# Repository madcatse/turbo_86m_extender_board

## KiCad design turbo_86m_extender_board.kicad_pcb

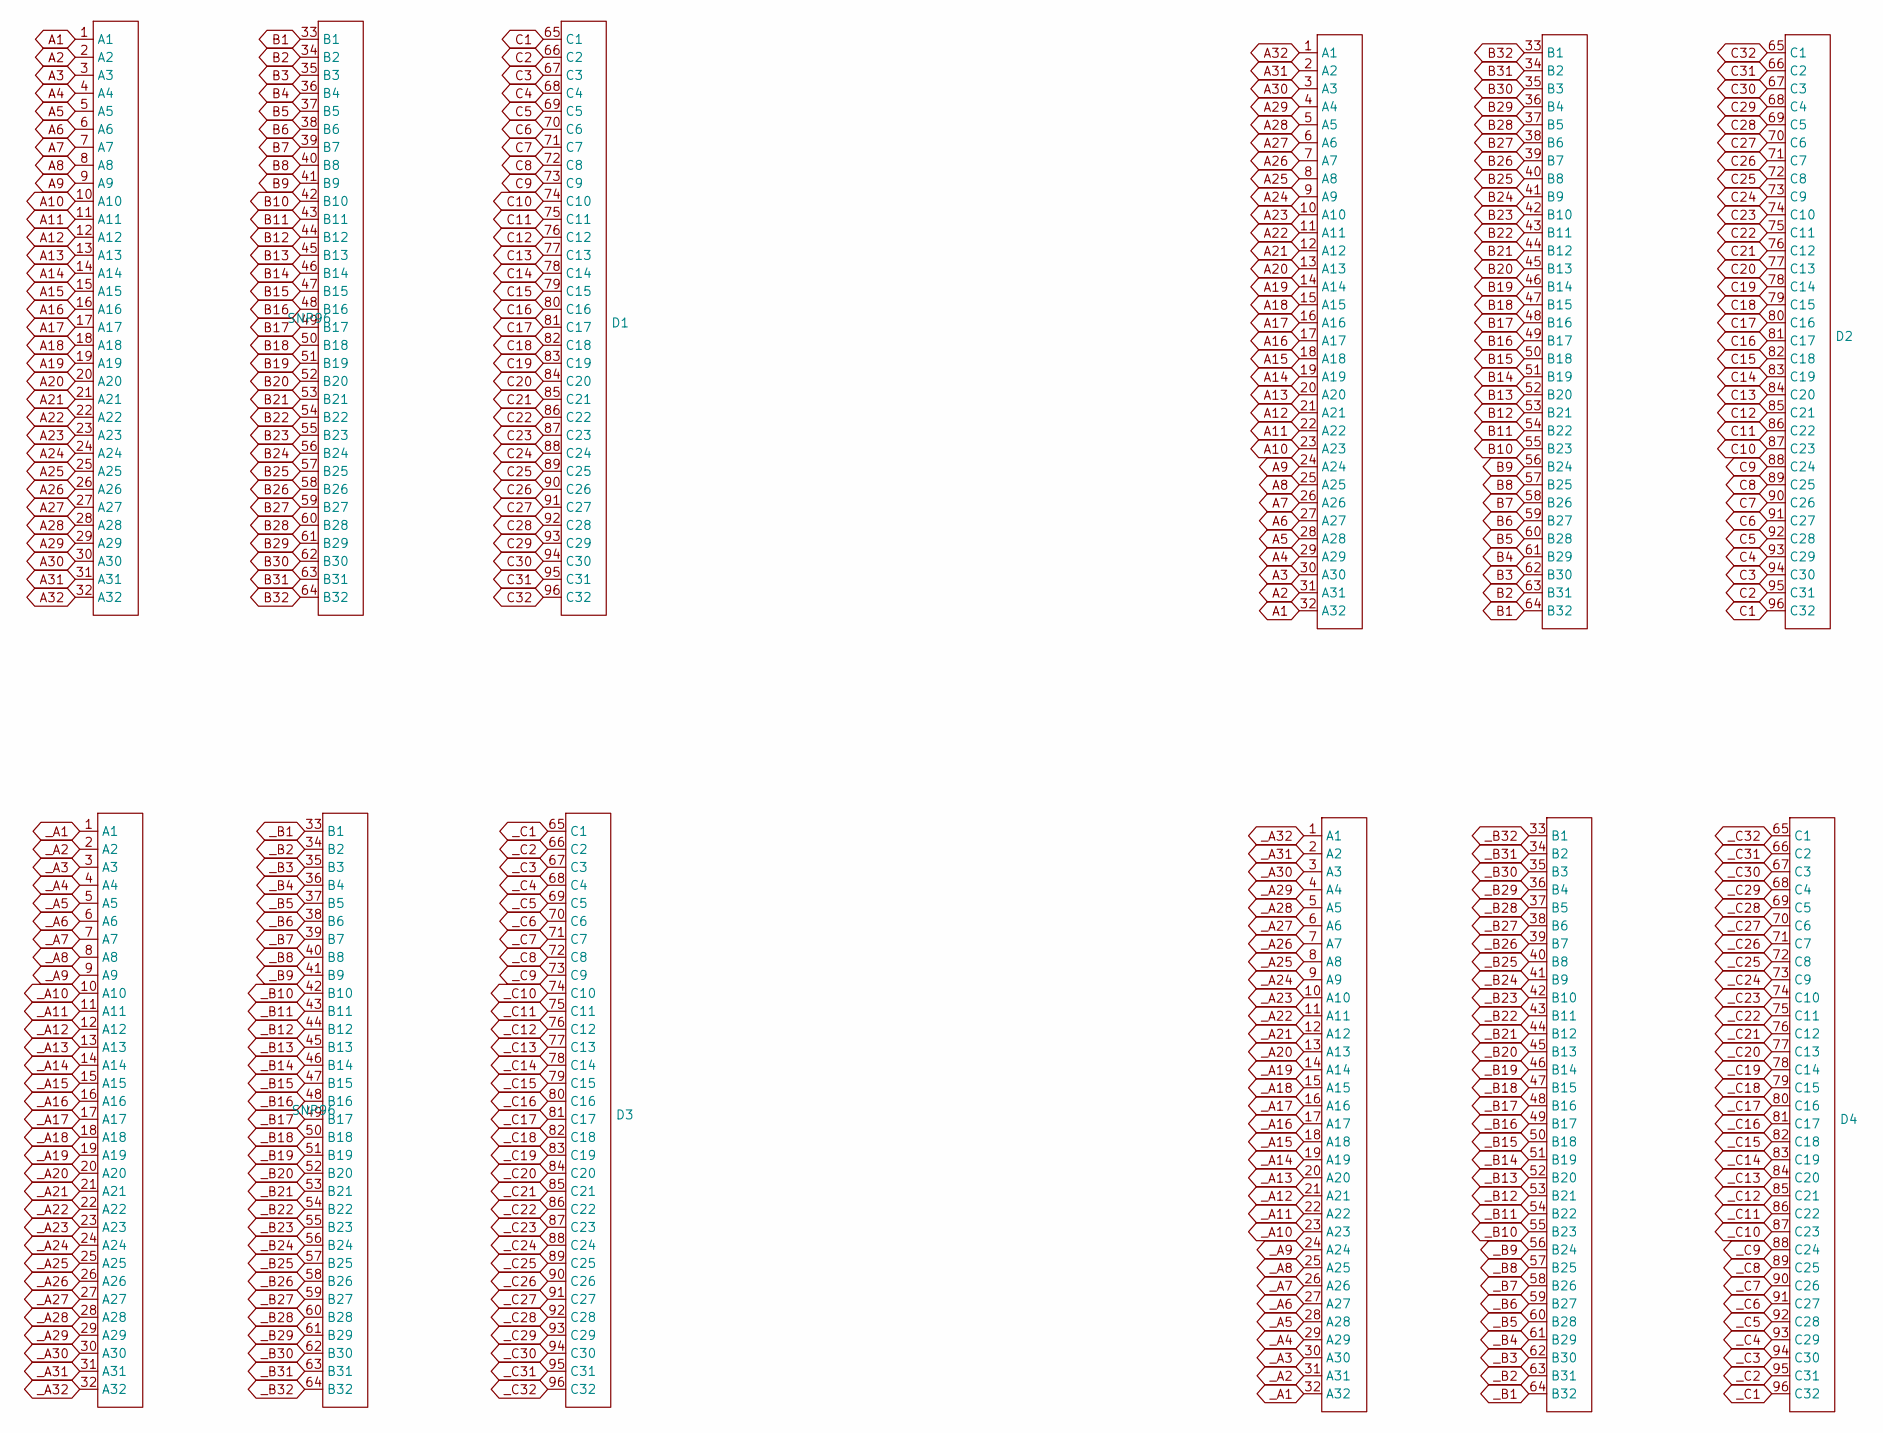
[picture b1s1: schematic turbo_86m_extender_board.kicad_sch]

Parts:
D1, D2, D3, D4: SNP96; snp59_96_female_angle

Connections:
A1: D1.1 (A1), D2.32 (A32)
A2: D1.2 (A2), D2.31 (A31)
A3: D1.3 (A3), D2.30 (A30)
A4: D1.4 (A4), D2.29 (A29)
A5: D1.5 (A5), D2.28 (A28)
A6: D1.6 (A6), D2.27 (A27)
A7: D1.7 (A7), D2.26 (A26)
A8: D1.8 (A8), D2.25 (A25)
A9: D1.9 (A9), D2.24 (A24)
A10: D1.10 (A10), D2.23 (A23)
A11: D1.11 (A11), D2.22 (A22)
A12: D1.12 (A12), D2.21 (A21)
A13: D1.13 (A13), D2.20 (A20)
A14: D1.14 (A14), D2.19 (A19)
A15: D1.15 (A15), D2.18 (A18)
A16: D1.16 (A16), D2.17 (A17)
A17: D1.17 (A17), D2.16 (A16)
A18: D1.18 (A18), D2.15 (A15)
A19: D1.19 (A19), D2.14 (A14)
A20: D1.20 (A20), D2.13 (A13)
A21: D1.21 (A21), D2.12 (A12)
A22: D1.22 (A22), D2.11 (A11)
A23: D1.23 (A23), D2.10 (A10)
A24: D1.24 (A24), D2.9 (A9)
A25: D1.25 (A25), D2.8 (A8)
A26: D1.26 (A26), D2.7 (A7)
A27: D1.27 (A27), D2.6 (A6)
A28: D1.28 (A28), D2.5 (A5)
A29: D1.29 (A29), D2.4 (A4)
A30: D1.30 (A30), D2.3 (A3)
A31: D1.31 (A31), D2.2 (A2)
A32: D1.32 (A32), D2.1 (A1)
B1: D1.33 (B1), D2.64 (B32)
B2: D1.34 (B2), D2.63 (B31)
B3: D1.35 (B3), D2.62 (B30)
B4: D1.36 (B4), D2.61 (B29)
B5: D1.37 (B5), D2.60 (B28)
B6: D1.38 (B6), D2.59 (B27)
B7: D1.39 (B7), D2.58 (B26)
B8: D1.40 (B8), D2.57 (B25)
B9: D1.41 (B9), D2.56 (B24)
B10: D1.42 (B10), D2.55 (B23)
B11: D1.43 (B11), D2.54 (B22)
B12: D1.44 (B12), D2.53 (B21)
B13: D1.45 (B13), D2.52 (B20)
B14: D1.46 (B14), D2.51 (B19)
B15: D1.47 (B15), D2.50 (B18)
B16: D1.48 (B16), D2.49 (B17)
B17: D1.49 (B17), D2.48 (B16)
B18: D1.50 (B18), D2.47 (B15)
B19: D1.51 (B19), D2.46 (B14)
B20: D1.52 (B20), D2.45 (B13)
B21: D1.53 (B21), D2.44 (B12)
B22: D1.54 (B22), D2.43 (B11)
B23: D1.55 (B23), D2.42 (B10)
B24: D1.56 (B24), D2.41 (B9)
B25: D1.57 (B25), D2.40 (B8)
B26: D1.58 (B26), D2.39 (B7)
B27: D1.59 (B27), D2.38 (B6)
B28: D1.60 (B28), D2.37 (B5)
B29: D1.61 (B29), D2.36 (B4)
B30: D1.62 (B30), D2.35 (B3)
B31: D1.63 (B31), D2.34 (B2)
B32: D1.64 (B32), D2.33 (B1)
C1: D1.65 (C1), D2.96 (C32)
C2: D1.66 (C2), D2.95 (C31)
C3: D1.67 (C3), D2.94 (C30)
C4: D1.68 (C4), D2.93 (C29)
C5: D1.69 (C5), D2.92 (C28)
C6: D1.70 (C6), D2.91 (C27)
C7: D1.71 (C7), D2.90 (C26)
C8: D1.72 (C8), D2.89 (C25)
C9: D1.73 (C9), D2.88 (C24)
C10: D1.74 (C10), D2.87 (C23)
C11: D1.75 (C11), D2.86 (C22)
C12: D1.76 (C12), D2.85 (C21)
C13: D1.77 (C13), D2.84 (C20)
C14: D1.78 (C14), D2.83 (C19)
C15: D1.79 (C15), D2.82 (C18)
C16: D1.80 (C16), D2.81 (C17)
C17: D1.81 (C17), D2.80 (C16)
C18: D1.82 (C18), D2.79 (C15)
C19: D1.83 (C19), D2.78 (C14)
C20: D1.84 (C20), D2.77 (C13)
C21: D1.85 (C21), D2.76 (C12)
C22: D1.86 (C22), D2.75 (C11)
C23: D1.87 (C23), D2.74 (C10)
C24: D1.88 (C24), D2.73 (C9)
C25: D1.89 (C25), D2.72 (C8)
C26: D1.90 (C26), D2.71 (C7)
C27: D1.91 (C27), D2.70 (C6)
C28: D1.92 (C28), D2.69 (C5)
C29: D1.93 (C29), D2.68 (C4)
C30: D1.94 (C30), D2.67 (C3)
C31: D1.95 (C31), D2.66 (C2)
C32: D1.96 (C32), D2.65 (C1)
_A1: D3.1 (A1), D4.32 (A32)
_A2: D3.2 (A2), D4.31 (A31)
_A3: D3.3 (A3), D4.30 (A30)
_A4: D3.4 (A4), D4.29 (A29)
_A5: D3.5 (A5), D4.28 (A28)
_A6: D3.6 (A6), D4.27 (A27)
_A7: D3.7 (A7), D4.26 (A26)
_A8: D3.8 (A8), D4.25 (A25)
_A9: D3.9 (A9), D4.24 (A24)
_A10: D3.10 (A10), D4.23 (A23)
_A11: D3.11 (A11), D4.22 (A22)
_A12: D3.12 (A12), D4.21 (A21)
_A13: D3.13 (A13), D4.20 (A20)
_A14: D3.14 (A14), D4.19 (A19)
_A15: D3.15 (A15), D4.18 (A18)
_A16: D3.16 (A16), D4.17 (A17)
_A17: D3.17 (A17), D4.16 (A16)
_A18: D3.18 (A18), D4.15 (A15)
_A19: D3.19 (A19), D4.14 (A14)
_A20: D3.20 (A20), D4.13 (A13)
_A21: D3.21 (A21), D4.12 (A12)
_A22: D3.22 (A22), D4.11 (A11)
_A23: D3.23 (A23), D4.10 (A10)
_A24: D3.24 (A24), D4.9 (A9)
_A25: D3.25 (A25), D4.8 (A8)
_A26: D3.26 (A26), D4.7 (A7)
_A27: D3.27 (A27), D4.6 (A6)
_A28: D3.28 (A28), D4.5 (A5)
_A29: D3.29 (A29), D4.4 (A4)
_A30: D3.30 (A30), D4.3 (A3)
_A31: D3.31 (A31), D4.2 (A2)
_A32: D3.32 (A32), D4.1 (A1)
_B1: D3.33 (B1), D4.64 (B32)
_B2: D3.34 (B2), D4.63 (B31)
_B3: D3.35 (B3), D4.62 (B30)
_B4: D3.36 (B4), D4.61 (B29)
_B5: D3.37 (B5), D4.60 (B28)
_B6: D3.38 (B6), D4.59 (B27)
_B7: D3.39 (B7), D4.58 (B26)
_B8: D3.40 (B8), D4.57 (B25)
_B9: D3.41 (B9), D4.56 (B24)
_B10: D3.42 (B10), D4.55 (B23)
_B11: D3.43 (B11), D4.54 (B22)
_B12: D3.44 (B12), D4.53 (B21)
_B13: D3.45 (B13), D4.52 (B20)
_B14: D3.46 (B14), D4.51 (B19)
_B15: D3.47 (B15), D4.50 (B18)
_B16: D3.48 (B16), D4.49 (B17)
_B17: D3.49 (B17), D4.48 (B16)
_B18: D3.50 (B18), D4.47 (B15)
_B19: D3.51 (B19), D4.46 (B14)
_B20: D3.52 (B20), D4.45 (B13)
_B21: D3.53 (B21), D4.44 (B12)
_B22: D3.54 (B22), D4.43 (B11)
_B23: D3.55 (B23), D4.42 (B10)
_B24: D3.56 (B24), D4.41 (B9)
_B25: D3.57 (B25), D4.40 (B8)
_B26: D3.58 (B26), D4.39 (B7)
_B27: D3.59 (B27), D4.38 (B6)
_B28: D3.60 (B28), D4.37 (B5)
_B29: D3.61 (B29), D4.36 (B4)
_B30: D3.62 (B30), D4.35 (B3)
_B31: D3.63 (B31), D4.34 (B2)
_B32: D3.64 (B32), D4.33 (B1)
_C1: D3.65 (C1), D4.96 (C32)
_C2: D3.66 (C2), D4.95 (C31)
_C3: D3.67 (C3), D4.94 (C30)
_C4: D3.68 (C4), D4.93 (C29)
_C5: D3.69 (C5), D4.92 (C28)
_C6: D3.70 (C6), D4.91 (C27)
_C7: D3.71 (C7), D4.90 (C26)
_C8: D3.72 (C8), D4.89 (C25)
_C9: D3.73 (C9), D4.88 (C24)
_C10: D3.74 (C10), D4.87 (C23)
_C11: D3.75 (C11), D4.86 (C22)
_C12: D3.76 (C12), D4.85 (C21)
_C13: D3.77 (C13), D4.84 (C20)
_C14: D3.78 (C14), D4.83 (C19)
_C15: D3.79 (C15), D4.82 (C18)
_C16: D3.80 (C16), D4.81 (C17)
_C17: D3.81 (C17), D4.80 (C16)
_C18: D3.82 (C18), D4.79 (C15)
_C19: D3.83 (C19), D4.78 (C14)
_C20: D3.84 (C20), D4.77 (C13)
_C21: D3.85 (C21), D4.76 (C12)
_C22: D3.86 (C22), D4.75 (C11)
_C23: D3.87 (C23), D4.74 (C10)
_C24: D3.88 (C24), D4.73 (C9)
_C25: D3.89 (C25), D4.72 (C8)
_C26: D3.90 (C26), D4.71 (C7)
_C27: D3.91 (C27), D4.70 (C6)
_C28: D3.92 (C28), D4.69 (C5)
_C29: D3.93 (C29), D4.68 (C4)
_C30: D3.94 (C30), D4.67 (C3)
_C31: D3.95 (C31), D4.66 (C2)
_C32: D3.96 (C32), D4.65 (C1)

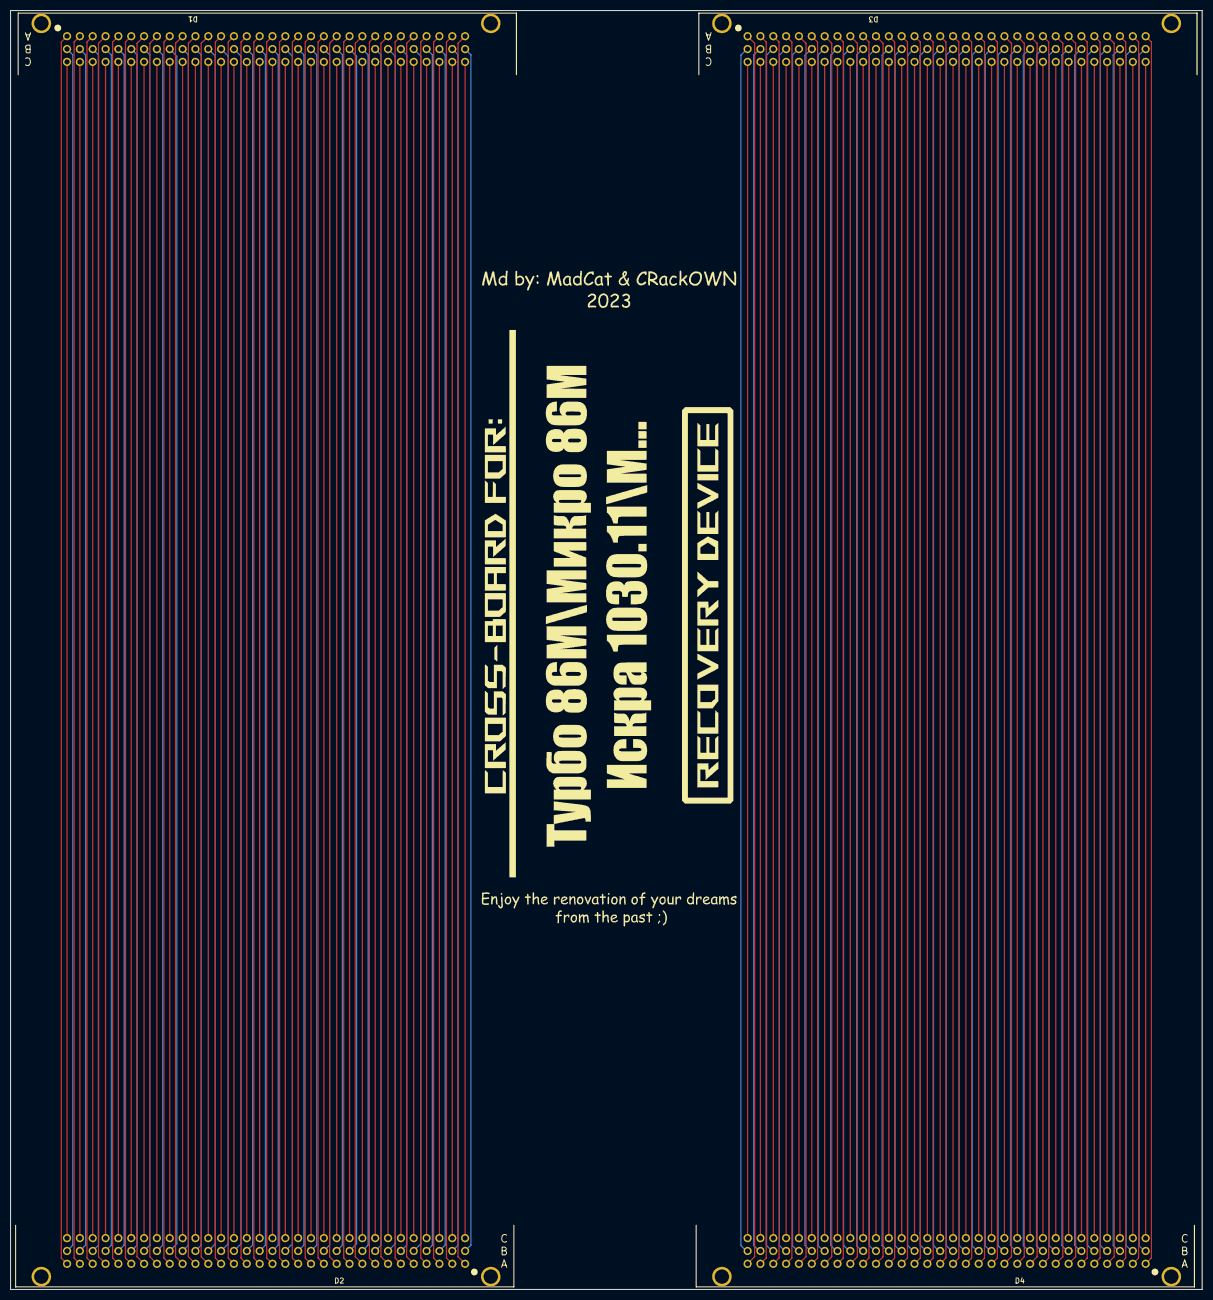
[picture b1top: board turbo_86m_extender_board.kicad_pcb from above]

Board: 2 copper layers, 232.0 x 249.0 mm, 4 parts (0 on the bottom side), 192 nets.

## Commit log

2023-10-12 Initial upload
2023-10-12 Ver. 0.1
2023-10-17 Updated gerbers
2023-10-17 Gerbers
